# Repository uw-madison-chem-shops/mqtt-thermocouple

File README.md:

# MQTT thermocouple

Simple project for getting thermocouple sensors online using MQTT.

Designed to work with [mqtt.chem.wisc.edu](https://mqtt.chem.wisc.edu/).

## Repository

This is an open source hardware project licensed under the CERN Open Hardware Licence Version 2 - Permissive.
Please see the LICENSE file for the complete license.

This repository is being mirrored to several version control systems in an attempt to ensure maximum avaliability.

| name             | url                                                        |
| ---------------- | ---------------------------------------------------------- |
| GitHub (primary) | https://github.com/uw-madison-chem-shops/mqtt-thermocouple |
| GitLab           | https://gitlab.com/uw-madison-chem-shops/mqtt-thermocouple |

## PCB

This PCB was designed using KiCAD version 5.
Refer to `mqtt-thermocouple.pdf` for schematic.
Refer to `mqtt-thermocouple.csv` for bill of materials.
PCB images generated with [tracespace](https://github.com/tracespace/tracespace) follow.

## Firmware

This project uses [micropython](https://micropython.org/), specifically [microhomie](https://github.com/microhomie/microhomie).
Refer to the "firmware" directory in this repository for detailed instructions.

## Changelog

### Unprinted

### B

#### added
- oshw logo
- github link

#### fixed
- resized holes for mounting piece
- added i2c pull up resistors

### A

#### Added
- initial design

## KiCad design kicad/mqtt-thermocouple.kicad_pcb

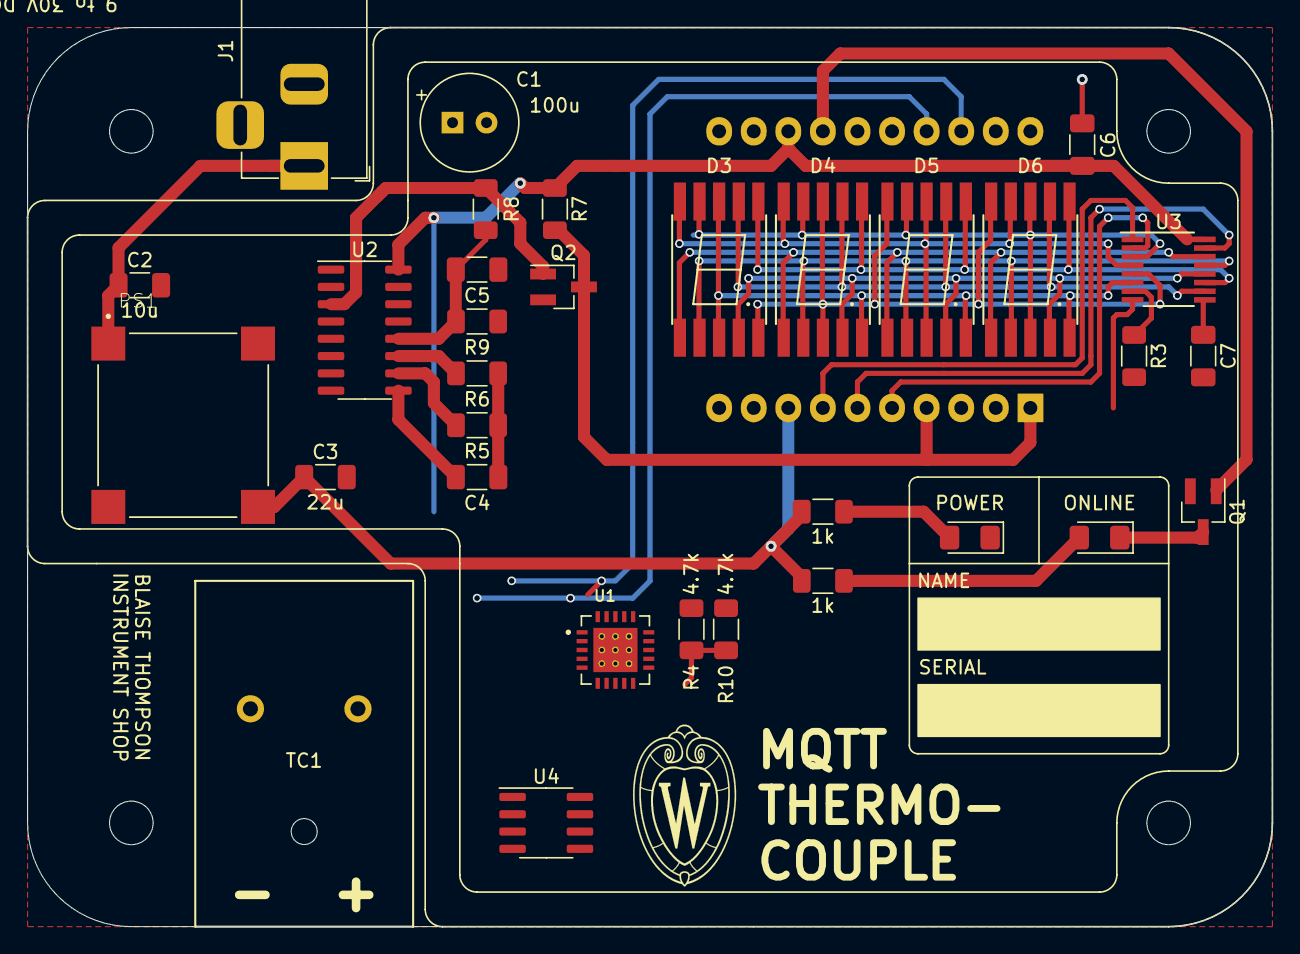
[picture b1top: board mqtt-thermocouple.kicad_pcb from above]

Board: 2 copper layers, 91.4 x 66.0 mm, 33 parts (1 on the bottom side), 33 nets.

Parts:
A1: Adafruit_HUZZAH_ESP8266_breakout
C1: 100u; CP_Radial_Tantal_D7.0mm_P2.50mm
C2: 10u; C_1206_3216Metric_Pad1.33x1.80mm_HandSolder
C3: 22u; C_1206_3216Metric_Pad1.33x1.80mm_HandSolder
C4, C5: 1u; C_1206_3216Metric_Pad1.33x1.80mm_HandSolder
C6: 100n; C_1206_3216Metric_Pad1.33x1.80mm_HandSolder
C7: 20p; C_1206_3216Metric_Pad1.33x1.80mm_HandSolder
D1, D2: LED; LED_1206_3216Metric_Pad1.42x1.75mm_HandSolder
D3, D4, D5, D6: ACSC02-41SURKWA-F01
J1: Barrel_Jack; BarrelJack_Horizontal
PS1: VXO7805-500-M; CONV_VXO7805-500-M
Q1, Q2: 2N7000; SOT-23_Handsoldering
R1, R2: 1k; R_1206_3216Metric_Pad1.30x1.75mm_HandSolder
R3: 100k; R_1206_3216Metric_Pad1.30x1.75mm_HandSolder
R4, R7, R8, R10: 4.7k; R_1206_3216Metric_Pad1.30x1.75mm_HandSolder
R5: 470k; R_1206_3216Metric_Pad1.30x1.75mm_HandSolder
R6, R9: 1M; R_1206_3216Metric_Pad1.30x1.75mm_HandSolder
TC1: Thermocouple; K1X-FEMX-CON-FP-X-PCCX
U1: MCP9600-E_MX; MX
U2: CD4060BM96; SOIC-16_3.9x9.9mm_P1.27mm
U3: MAX6951; QSOP-16_3.9x4.9mm_P0.635mm
U4: MAX31855KASA; SOIC-8_3.9x4.9mm_P1.27mm

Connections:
+3V3: A1.13 (3V), C6.1, R4.1, R7.1, R10.1, U1.8 (VDD), U2.16 (VDD), U3.16 (V+)
+5V: A1.8 (V+), C3.1, PS1.3 (+VO), R1.1, R2.1
/display/SEG0: D3.3 (C.K.), D3.8 (C.K.), D4.5 (DP), D5.5 (DP), D6.5 (DP), U3.6 (DIG0/SEG0)
/display/SEG1: D3.5 (DP), D4.3 (C.K.), D4.8 (C.K.), D5.10 (g), D6.10 (g), U3.5 (DIG1/SEG1)
/display/SEG2: D3.10 (g), D4.10 (g), D5.3 (C.K.), D5.8 (C.K.), D6.9 (f), U3.4 (DIG2/SEG2)
/display/SEG3: D3.9 (f), D4.9 (f), D5.9 (f), D6.3 (C.K.), D6.8 (C.K.), U3.3 (DIG3/SEG3)
/display/SEG4: D3.1 (e), D4.1 (e), D5.1 (e), D6.1 (e), U3.14 (DIG4/SEG4)
/display/SEG5: D3.2 (d), D4.2 (d), D5.2 (d), D6.2 (d), U3.13 (DIG5/SEG5)
/display/SEG6: D3.4 (c), D4.4 (c), D5.4 (c), D6.4 (c), U3.12 (DIG6/SEG6)
/display/SEG7: D3.6 (b), D4.6 (b), D5.6 (b), D6.6 (b), U3.11 (DIG7/SEG7)
/display/SEG8: D3.7 (a), D4.7 (a), D5.7 (a), D6.7 (a), U3.10 (SEG8)
/display/~CS: A1.6 (12), U3.15 (~CS)
GND: A1.10 (GND), A1.11 (GND), C1.2, C2.2, C3.2, C5.2, C6.2, C7.2, D1.1 (K), J1.2, PS1.2 (GND), Q1.2 (S), Q2.2 (S), R3.2, R9.2, U1.1 (GND), U1.3 (GND), U1.5 (GND), U1.6 (GND), U1.7 (GND), U1.9 (GND), U1.10 (GND), U1.13 (GND), U1.16 (ADDR), U1.17 (GND), U1.18 (GND), U2.8 (GND), U3.8 (GND)
MOSI: A1.7 (13), U3.1 (DIN)
unnamed: A1.1 (~RST), A1.4 (16), Q2.3 (D), R7.2
unnamed: A1.16 (0), Q1.1 (G)
unnamed: C1.1, C2.1, J1.1, PS1.1 (+VIN)
unnamed: C4.1, U2.9 (CLK_0-1)
unnamed: C4.2, R5.1, R6.1
unnamed: C5.1, R8.2, R9.1, U2.12 (RST)
unnamed: C7.1, U3.9 (OSC)
unnamed: D1.2 (A), R1.2
unnamed: D2.1 (K), Q1.3 (D)
unnamed: D2.2 (A), R2.2
unnamed: Q2.1 (G), R8.1, U2.3 (Q14)
unnamed: R3.1, U3.7 (ISET)
unnamed: R5.2, U2.10 (CLK_0)
unnamed: R6.2, U2.11 (CLK_1)
unnamed: TC1.1 (+), U1.2 (VIN+)
unnamed: TC1.2 (-), U1.4 (VIN-)
SCK: A1.5 (14), U3.2 (CLK)
SCL: A1.18 (5), R10.2, U1.19 (SCL)
SDA: A1.17 (4), R4.2, U1.20 (SDA)

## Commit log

2021-07-02 README
2021-07-02 license
2021-07-02 basic schematic and incomplete layout
2021-07-02 urls
2021-07-06 revision A
2021-07-09 forgotten fill
2022-04-22 revB
2022-04-22 tracespace rerender
2022-06-28 potting-bracket
2023-02-28 checkpoint
